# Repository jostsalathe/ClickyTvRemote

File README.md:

# ClickyTvRemote
A custom IR TV remote with mechanical keyboard switches

The project started because we have no remote any more for our Philips 32PFL5403D/12 TV.

IR codes for this Model can be found in the [IRDB on Github](https://github.com/probonopd/irdb/blob/master/codes/Philips/Unknown_32PFL5403D/0%2C-1.csv).

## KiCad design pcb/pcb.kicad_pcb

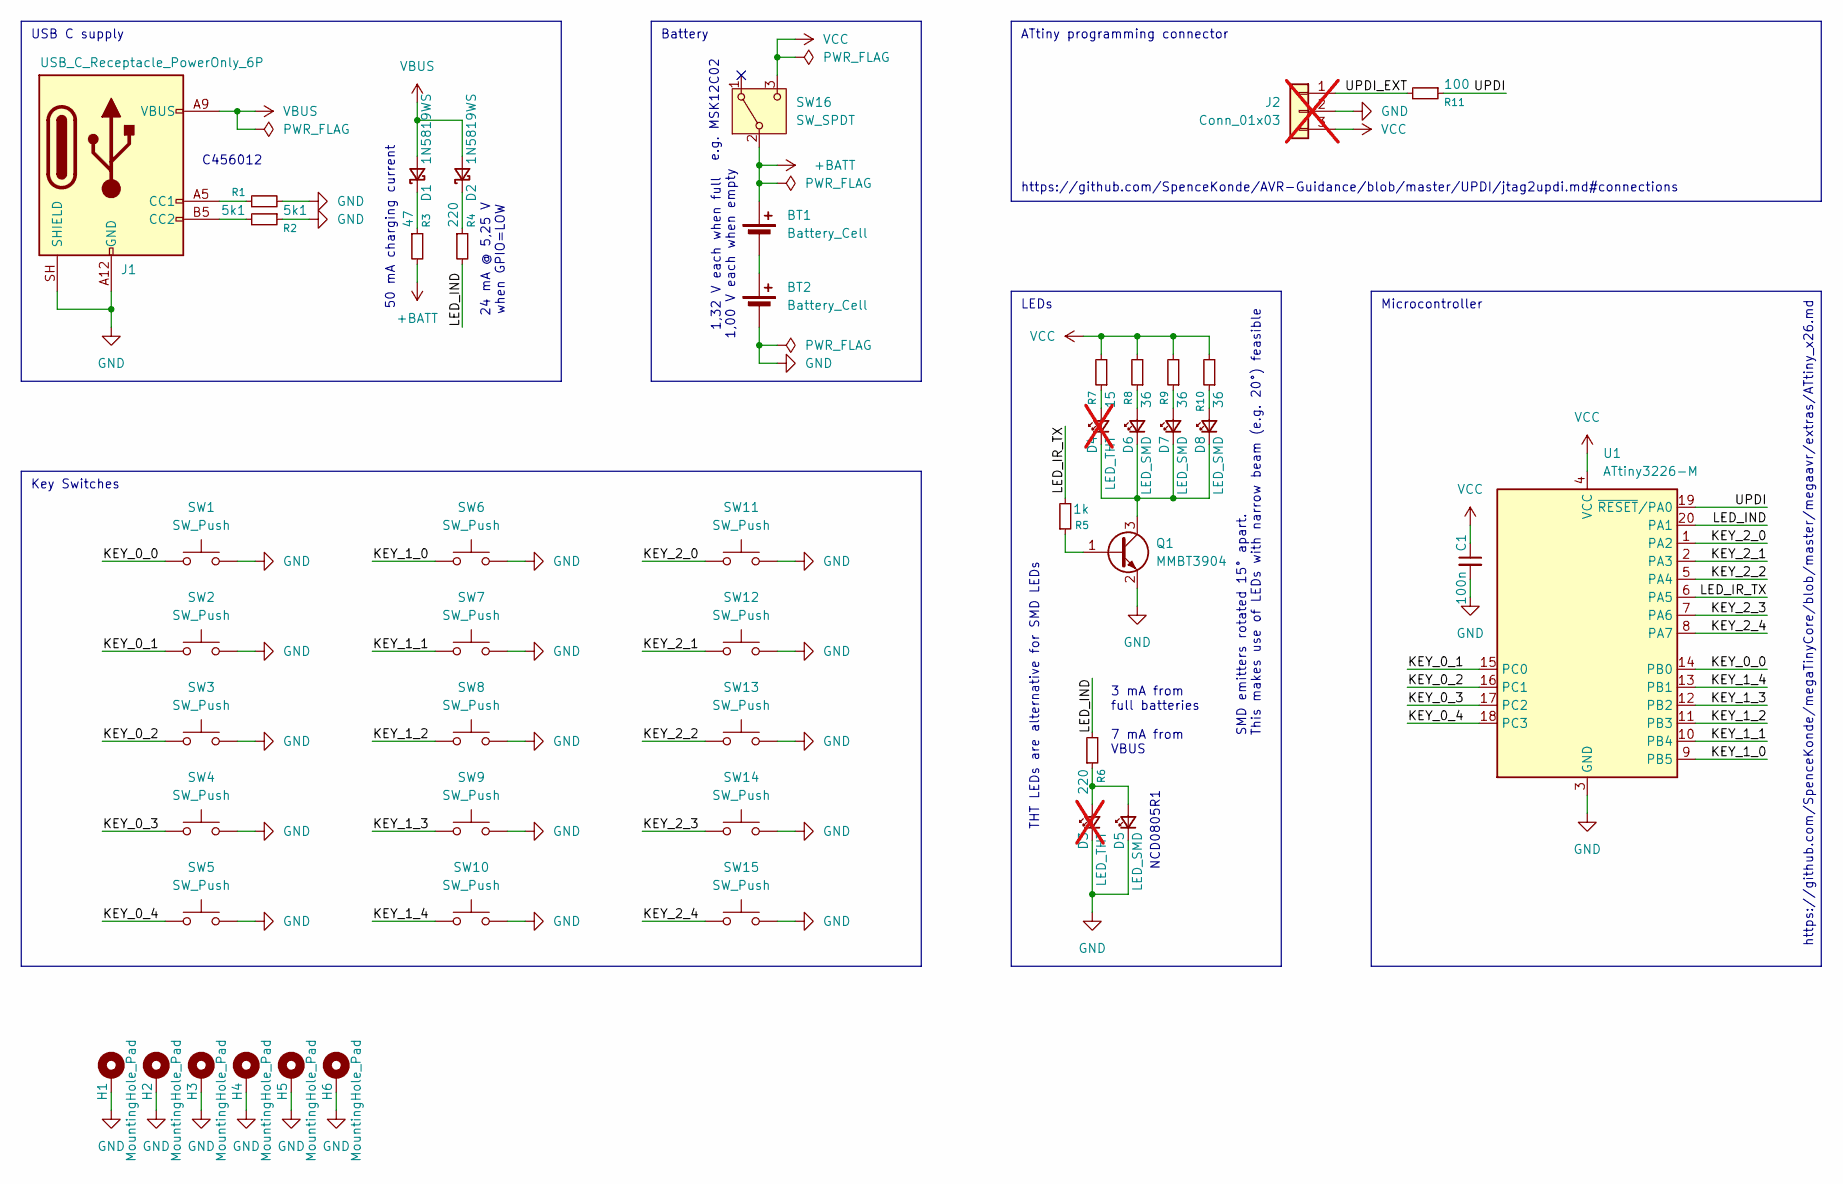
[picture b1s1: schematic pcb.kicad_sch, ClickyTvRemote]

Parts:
BT1, BT2: Battery_Cell; MYOUNG_AA_BH-AA-B5BA026; LCSC C20606794
C1: 100n; C_0603_1608Metric_Pad1.08x0.95mm_HandSolder; LCSC C14663
D1, D2: 1N5819WS; D_SOD-323_HandSoldering; LCSC C191023
D3: LED_THT; LED_D3.0mm; not fitted
D4: LED_THT; LED_D3.0mm_Horizontal_O1.27mm_Z2.0mm_IRBlack; not fitted
D5: LED_SMD; LED_0805_2012Metric_Pad1.15x1.40mm_HandSolder; LCSC C84256
D6, D7, D8: LED_SMD; IR12-21CTR8; LCSC C53672
H1, H2, H3, H4, H5, H6: MountingHole_Pad; MountingHole_3.2mm_M3_Pad_Via
J1: USB_C_Receptacle_PowerOnly_6P; USB_C_Receptacle_HRO_TYPE-C-31-M-17; LCSC C456012
J2: Conn_01x03; PinSocket_1x03_P2.54mm_Horizontal; not fitted
Q1: MMBT3904; SOT-23_Handsoldering; LCSC C20526
R1, R2: 5k1; R_0603_1608Metric_Pad0.98x0.95mm_HandSolder; LCSC C23186
R3: 47; R_0603_1608Metric_Pad0.98x0.95mm_HandSolder; LCSC C23182
R4, R6: 220; R_0603_1608Metric_Pad0.98x0.95mm_HandSolder; LCSC C22962
R5: 1k; R_0603_1608Metric_Pad0.98x0.95mm_HandSolder; LCSC C21190
R7: 15; R_0603_1608Metric_Pad0.98x0.95mm_HandSolder; LCSC C22810
R8, R9, R10: 36; R_0603_1608Metric_Pad0.98x0.95mm_HandSolder; LCSC C23148
R11: 100; R_0603_1608Metric_Pad0.98x0.95mm_HandSolder; LCSC C22775
SW1, SW2, SW3, SW4, SW5, SW6, SW7, SW8, SW9, SW10, SW11, SW12, SW13, SW14, SW15: SW_Push; SW_Cherry_MX_1.00u_PCB
SW16: SW_SPDT; SW_SPDT_PCM12; LCSC C431540
U1: ATtiny3226-M; VQFN-20-1EP_3x3mm_P0.4mm_EP1.7x1.7mm; LCSC C5227682

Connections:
+BATT: BT1.1 (+), R3.2, SW16.2 (B)
/KEY_0_0: SW1.1, U1.14 (PB0)
/KEY_0_1: SW2.1, U1.15 (PC0)
/KEY_0_2: SW3.1, U1.16 (PC1)
/KEY_0_3: SW4.1, U1.17 (PC2)
/KEY_0_4: SW5.1, U1.18 (PC3)
/KEY_1_0: SW6.1, U1.9 (PB5)
/KEY_1_1: SW7.1, U1.10 (PB4)
/KEY_1_2: SW8.1, U1.11 (PB3)
/KEY_1_3: SW9.1, U1.12 (PB2)
/KEY_1_4: SW10.1, U1.13 (PB1)
/KEY_2_0: SW11.1, U1.1 (PA2)
/KEY_2_1: SW12.1, U1.2 (PA3)
/KEY_2_2: SW13.1, U1.5 (PA4)
/KEY_2_3: SW14.1, U1.7 (PA6)
/KEY_2_4: SW15.1, U1.8 (PA7)
/LED_IND: R4.2, R6.2, U1.20 (PA1)
/LED_IR_TX: R5.2, U1.6 (PA5)
/UPDI: R11.1, U1.19 (~RESET/PA0)
/UPDI_EXT: J2.1, R11.2
GND: BT2.2 (-), C1.2, D3.1 (K), D5.1 (K), H1.1 (1_1), H2.1 (1_1), H3.1 (1_1), H4.1 (1_1), H5.1 (1_1), H6.1 (1_1), J1.A12 (GND), J1.B12 (GND), J1.SH (SHIELD), J2.2, Q1.2 (E), R1.2, R2.1, SW1.2, SW2.2, SW3.2, SW4.2, SW5.2, SW6.2, SW7.2, SW8.2, SW9.2, SW10.2, SW11.2, SW12.2, SW13.2, SW14.2, SW15.2, U1.3 (GND), U1.21 (GND)
unnamed: BT1.2 (-), BT2.1 (+)
unnamed: D1.1 (K), R3.1
unnamed: D2.1 (K), R4.1
unnamed: D3.2 (A), D5.2 (A), R6.1
unnamed: D4.2 (A), R7.1
unnamed: D4.1 (K), D6.1 (K), D7.1 (K), D8.1 (K), Q1.3 (C)
unnamed: D6.2 (A), R8.1
unnamed: D7.2 (A), R9.1
unnamed: D8.2 (A), R10.1
unnamed: J1.A5 (CC1), R1.1
unnamed: J1.B5 (CC2), R2.2
unnamed: Q1.1 (B), R5.1
VBUS: D1.2 (A), D2.2 (A), J1.A9 (VBUS), J1.B9 (VBUS)
VCC: C1.1, J2.3, R7.2, R8.2, R9.2, R10.2, SW16.3 (C), U1.4 (VCC)

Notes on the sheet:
Microcontroller
THT LEDs are alternative for SMD LEDs
Key Switches
https://github.com/SpenceKonde/megaTinyCore/blob/master/megaavr/extras/ATtiny_x26.md
https://github.com/SpenceKonde/AVR-Guidance/blob/master/UPDI/jtag2updi.md#connections
24 mA @ 5,25 V when GPIO=LOW
3 mA from full batteries 7 mA from VBUS
1,32 V each when full 1,00 V each when empty
e.g. MSK12C02
C456012
NCD0805R1
Battery
LEDs
USB C supply
ATtiny programming connector
SMD emitters rotated 15° apart. This makes use of LEDs with narrow beam (e.g. 20°) feasible
50 mA charging current

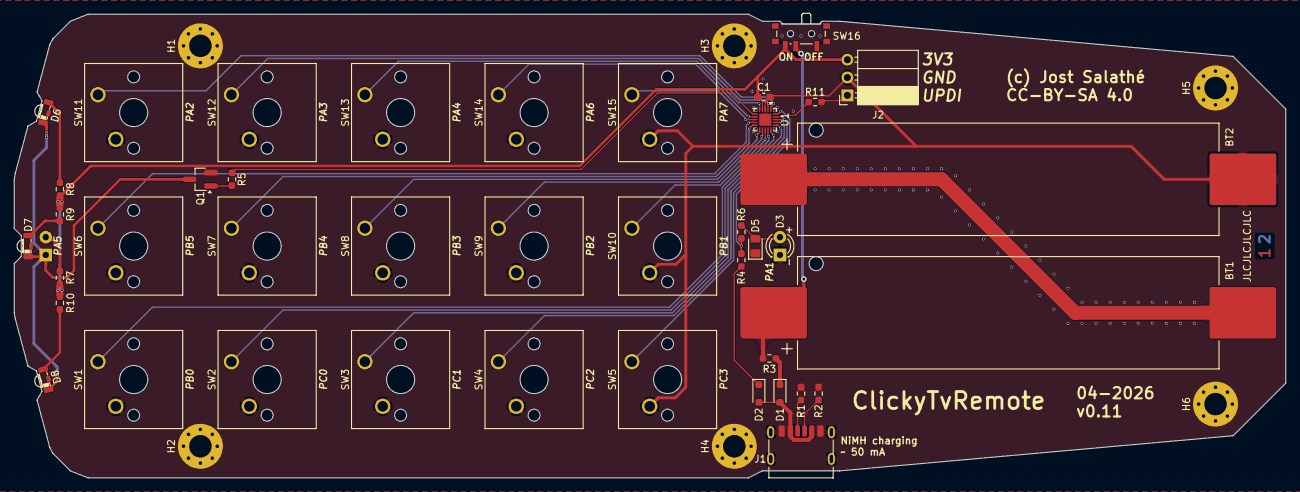
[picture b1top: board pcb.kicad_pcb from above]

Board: 2 copper layers, 181.0 x 66.0 mm, 48 parts (1 on the bottom side), 35 nets.

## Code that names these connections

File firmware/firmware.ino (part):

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#include <avr/sleep.h>


#define IR_SEND_PIN PIN_PA5

#define DISABLE_CODE_FOR_RECEIVER // Disables static receiver code like receive timer ISR handler and static IRReceiver and irparams data. Saves 450 bytes program memory and 269 bytes RAM if receiving functions are not required.
#define IR_USE_AVR_TIMER_A        // Fix because ATtiny3226 is not explicitly supported by the IRremote library, yet...

#undef LED_BUILTIN                // No LED defined in megaTinyCore
#define LED_BUILTIN PIN_PA1
//#define NO_LED_FEEDBACK_CODE      // Saves 216 bytes program memory

#ifdef NO_LED_FEEDBACK_CODE
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// codes for Philips 32PFL5403D according to IRDB
// https://github.com/probonopd/irdb/blob/master/codes/Philips/Unknown_32PFL5403D/0%2C-1.csv
static constexpr Command commands[] = {
  {PIN_PB0, 0xff, 0xff, "KEY_BAT"},        // KEY_0_0
  {PIN_PB5, 0, 12, "KEY_PWR"},             // KEY_1_0
  {PIN_PA2, 0, 12, "KEY_PWR"},             // KEY_2_0
  {PIN_PC0, 0, 32, "KEY_CHANNELUP"},       // KEY_0_1
  {PIN_PB4, 0, 16, "KEY_VOLUMEUP"},        // KEY_1_1
  {PIN_PA3, 0, 245, "KEY_Picture_Format"}, // KEY_2_1
  {PIN_PC1, 0, 33, "KEY_CHANNELDOWN"},     // KEY_0_2
  {PIN_PB3, 0, 17, "KEY_VOLUMEDOWN"},      // KEY_1_2
  {PIN_PA4, 0, 13, "KEY_MUTE"},            // KEY_2_2
  {PIN_PC2, 0, 84, "KEY_MENU"},            // KEY_0_3
  {PIN_PB2, 0, 88, "KEY_UP"},              // KEY_1_3
  {PIN_PA6, 0, 92, "KEY_OK"},              // KEY_2_3
  {PIN_PC3, 0, 90, "KEY_LEFT"},            // KEY_0_4
  {PIN_PB1, 0, 89, "KEY_DOWN"},            // KEY_1_4
  {PIN_PA7, 0, 91, "KEY_RIGHT"},           // KEY_2_4
};

// millivolt -> state of charge look up table for two NiMH cells
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  // after wakeup, disable interrupts and enable Pullups for all buttons
  setPinModes(false);

  ON_PRINT(Serial.pins(PIN_PA1, PIN_PA2));
  ON_PRINT(Serial.begin(230400, SERIAL_TX_ONLY));

  ON_PRINT(Serial.println());
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
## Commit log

2026-03-29 added the ATtiny3226, one switch and signal labels for all wanted switches
2026-03-29 added reference to IRDB to README.md
2026-03-29 migrated pcb design to KiCAD 10.0 and added some components
2026-03-29 added first firmware draft (for now just trying out stuff on an Arduino Nano)
2026-03-29 added indicator LED and correct labels for all signals
2026-03-29 fixed volume button direction
2026-03-29 slightly simplified key press handling
2026-04-03 added Function struct and improved press timing and repeat handling The new Function struct helps to better organize function definitions and key pin association as well as reduce code duplication. T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
2026-04-03 renamed functions to commands added command definitions as comments in preparation for the ATtiny pcb
2026-04-03 completed first draft of schematics
2026-04-04 fixed battery clip 3D model scale
2026-04-04 Added mounting holes and started work on layout
2026-04-04 Completed routing of all signals and rearranged key signals for better routing
2026-04-04 updated prepared commands keyPins according to rearranged signals in firmware.ino
2026-04-04 changed THT IR LED footprint in schematics for one that has less body offset
2026-04-04 completed layout with info texts and everything
2026-04-04 Added LCSC part numbers
2026-04-04 fixed DRC errors and warnings
2026-04-04 added JLCPCB order number place holder
2026-04-04 added JLCPCB production exports to .gitignore
2026-04-04 removed DRC exclusions
2026-04-04 resized JLCPCB order number place holder
2026-04-04 made vias larger to fall into cheaper manufacturing constraints
2026-04-07 fixed SMD indicator LED footprint changed from 1206 to 0805 size, because they are cheaper at JLCPCB
2026-04-07 added rendered image of PCB v0.11
2026-04-25 made Serial usage completely optional by introducing ON_PRINT(A) macro (disabled for now)
2026-04-25 changed over from Arduino Nano to ATtiny3226 pinout
2026-04-25 added define because IRremote is not yet officially compatible with ATtiny3226
2026-04-25 Add information about how to configure tinyMegaCore for compiling and flashing this project
2026-04-26 add thermal reliefs to BT2 Pad 2 (connected to GND plane)
2026-05-01 improved serial output facilities
2026-05-01 prepared some code for batteryreporting
2026-05-01 prepared some code for entering sleep mode
2026-05-01 completed power down and wakeup implementation
2026-05-01 completed battery voltage reading and serial printout
2026-05-01 added LUT for SOC approximation
2026-05-02 deepSleep() becomes powerDown()
2026-05-02 adjusted uBat measurement
2026-05-02 added SOC reporting via blinking indicator LED
2026-05-02 added back missing powerDown() call that was erroneously removed some commits ago
2026-05-02 delayed powerDown to 2 seconds after last activity so that rapid successive keypresses are actually interpreted by the receiving device

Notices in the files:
pcb/pcb.kicad_pcb:
CC-BY-SA 4.0
